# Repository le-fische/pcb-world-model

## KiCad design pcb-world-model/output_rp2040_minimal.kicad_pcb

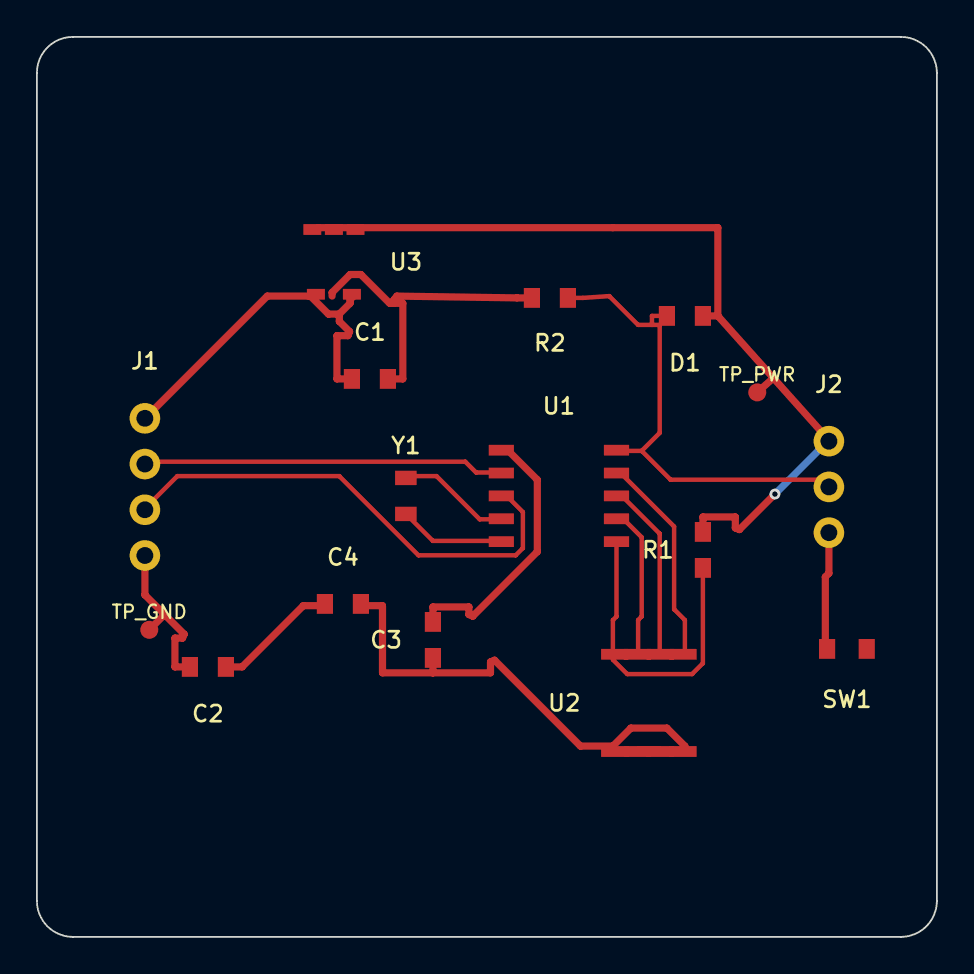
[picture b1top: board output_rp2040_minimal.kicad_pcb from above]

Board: 2 copper layers, 50.0 x 50.0 mm, 16 parts (0 on the bottom side), 12 nets.

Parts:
C1: 10uF_VBUS; C_0805_2012Metric
C2: 100nF_VDD; C_0805_2012Metric
C3: 100nF_CORE; C_0805_2012Metric
C4: 100nF_FLASH; C_0805_2012Metric
D1: PWR_LED; LED_0805_2012Metric
J1: USB_C; USB_C_Receptacle_GCT_USB4085
J2: GPIO_HDR; PinHeader_1x03_P2.54mm_Vertical
R1: 10k_CS; R_0603_1608Metric
R2: 1k_LED; R_0603_1608Metric
SW1: BOOTSEL; SW_SPST_TL3342
TP_GND: TestPoint_Pad_D1.0mm
TP_PWR: TestPoint_Pad_D1.0mm
U1: RP2040; QFN-10_RP2040_Core
U2: W25Q16JV; SOIC-8_3.9x4.9mm_P1.27mm
U3: NCP1117-3.3; SOT-23-5
Y1: 12MHz; Crystal_SMD_3225

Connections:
GND: C1.2, C2.2, C3.2, C4.2, J1.4, J2.3, R2.2, SW1.2, TP_GND.1, U2.5, U2.8, U3.2
LED_STAT: D1.2, J2.2, R2.1, U1.6
QSPI_CLK: U1.9, U2.3
QSPI_CS: R1.2, SW1.1, U1.10, U2.4
QSPI_D0: U1.8, U2.2
QSPI_D1: U1.7, U2.1
USB_DM: J1.2, U1.2
USB_DP: J1.3, U1.3
VBUS_5V: C1.1, J1.1, U3.1, U3.3
VCC_3V3: C2.1, C3.1, C4.1, D1.1, J2.1, R1.1, TP_PWR.1, U1.1, U2.6, U2.7, U3.4, U3.5
XIN: U1.4, Y1.1
XOUT: U1.5, Y1.2

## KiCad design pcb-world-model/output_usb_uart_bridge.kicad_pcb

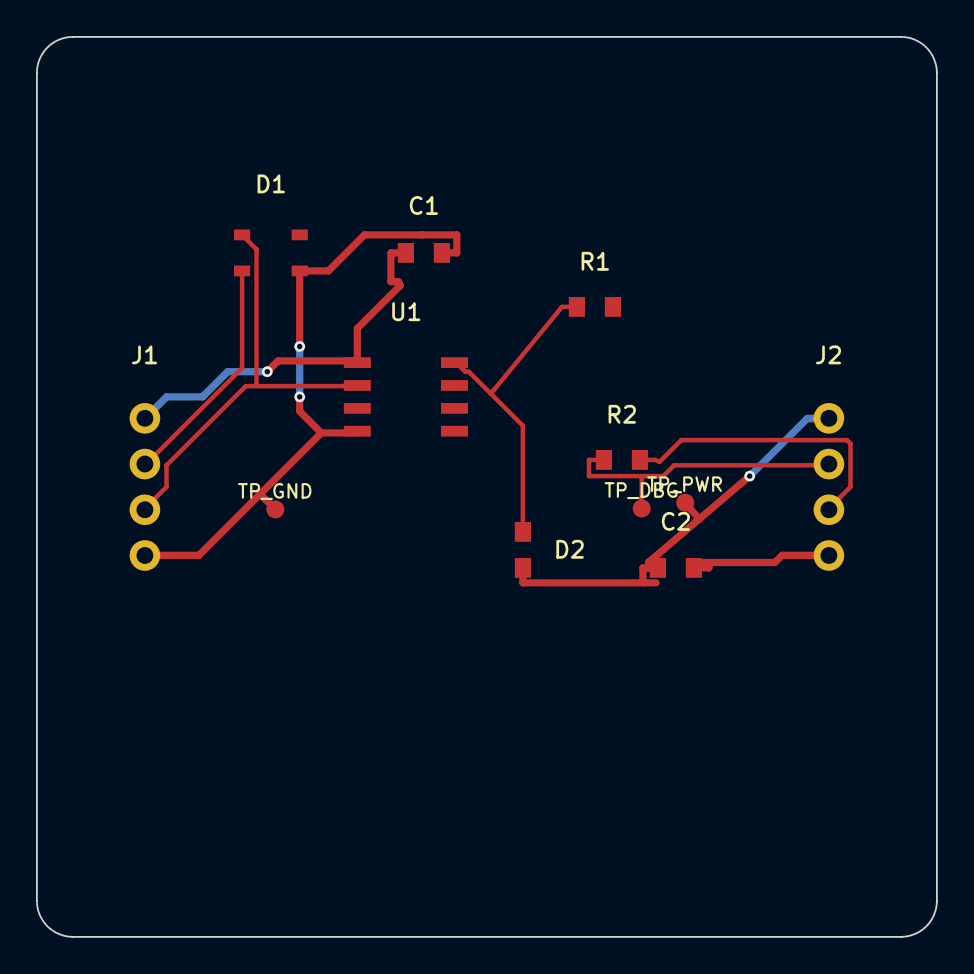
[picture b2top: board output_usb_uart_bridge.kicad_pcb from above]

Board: 2 copper layers, 50.0 x 50.0 mm, 12 parts (0 on the bottom side), 8 nets.

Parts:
C1: 10uF; C_0805_2012Metric
C2: 100nF; C_0805_2012Metric
D1: USBLC6-2SC6; SOT-23-6
D2: TX_LED; LED_0805_2012Metric
J1: USB_PORT; USB_Micro-B_Molex
J2: UART_HDR; PinHeader_1x04_P2.54mm_Vertical
R1: 470R; R_0603_1608Metric
R2: 0R_LOOP_OPT; R_0603_1608Metric
TP_DBG: TestPoint_Pad_D1.0mm
TP_GND: TestPoint_Pad_D1.0mm
TP_PWR: TestPoint_Pad_D1.0mm
U1: CH340N_BRIDGE; SOIC-8_3.9x4.9mm_P1.27mm

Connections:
GND: C1.2, C2.2, D1.3, J1.4, J2.4, R1.2, TP_GND.1, U1.4
LED_ACT: D2.2, R1.1, U1.8
UART_RX: J2.3, R2.2, U1.7
UART_TX: J2.2, R2.1, TP_DBG.1, U1.6
USB_DM: D1.2, J1.2, U1.3
USB_DP: D1.1, J1.3, U1.2
VBUS_5V: C1.1, D1.4, J1.1, U1.1
VCC_3V3: C2.1, D2.1, J2.1, TP_PWR.1, U1.5

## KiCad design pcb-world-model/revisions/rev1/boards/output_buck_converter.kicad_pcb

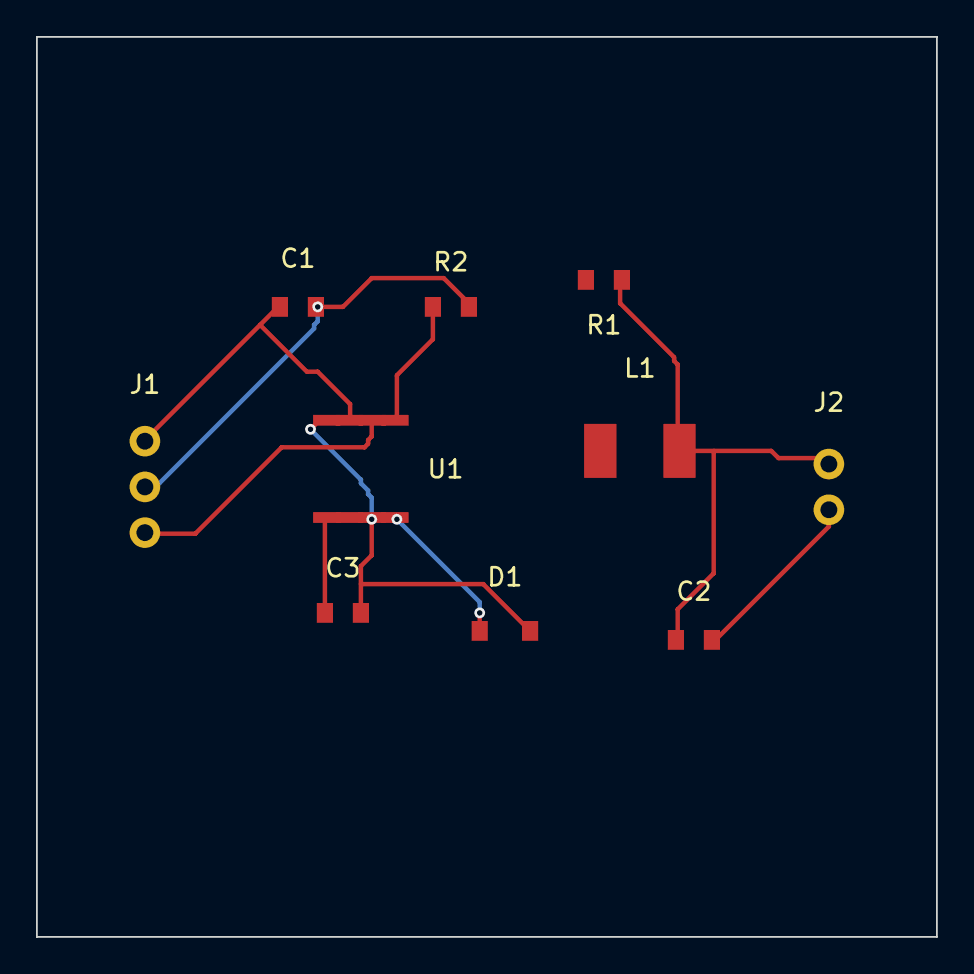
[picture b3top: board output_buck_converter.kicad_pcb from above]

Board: 2 copper layers, 50.0 x 50.0 mm, 10 parts (0 on the bottom side), 7 nets.

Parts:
C1: 22uF_IN; C_1206_3216Metric
C2: 47uF_OUT; C_1206_3216Metric
C3: 100nF_BST; C_0603_1608Metric
D1: SS34; D_SMA
J1: VIN_12V; TerminalBlock_bornier-3_P5.08mm
J2: VOUT_5V; TerminalBlock_bornier-2_P5.08mm
L1: 10uH; L_6.3x6.3_H3
R1: 100k; R_0603_1608Metric
R2: 18.7k; R_0603_1608Metric
U1: TPS54302; SOIC-8_3.9x4.9mm_P1.27mm

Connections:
BOOT: C3.1, U1.1
EN_CTRL: J1.3, U1.6
FB_DIV: R1.2, R2.1, U1.5
GND: C1.2, C2.2, D1.1, J1.2, J2.2, R2.2, U1.4
SW_NODE: C3.2, D1.2, L1.1, U1.3, U1.8
VIN_12V: C1.1, J1.1, U1.2, U1.7
VOUT_5V: C2.1, J2.1, L1.2, R1.1

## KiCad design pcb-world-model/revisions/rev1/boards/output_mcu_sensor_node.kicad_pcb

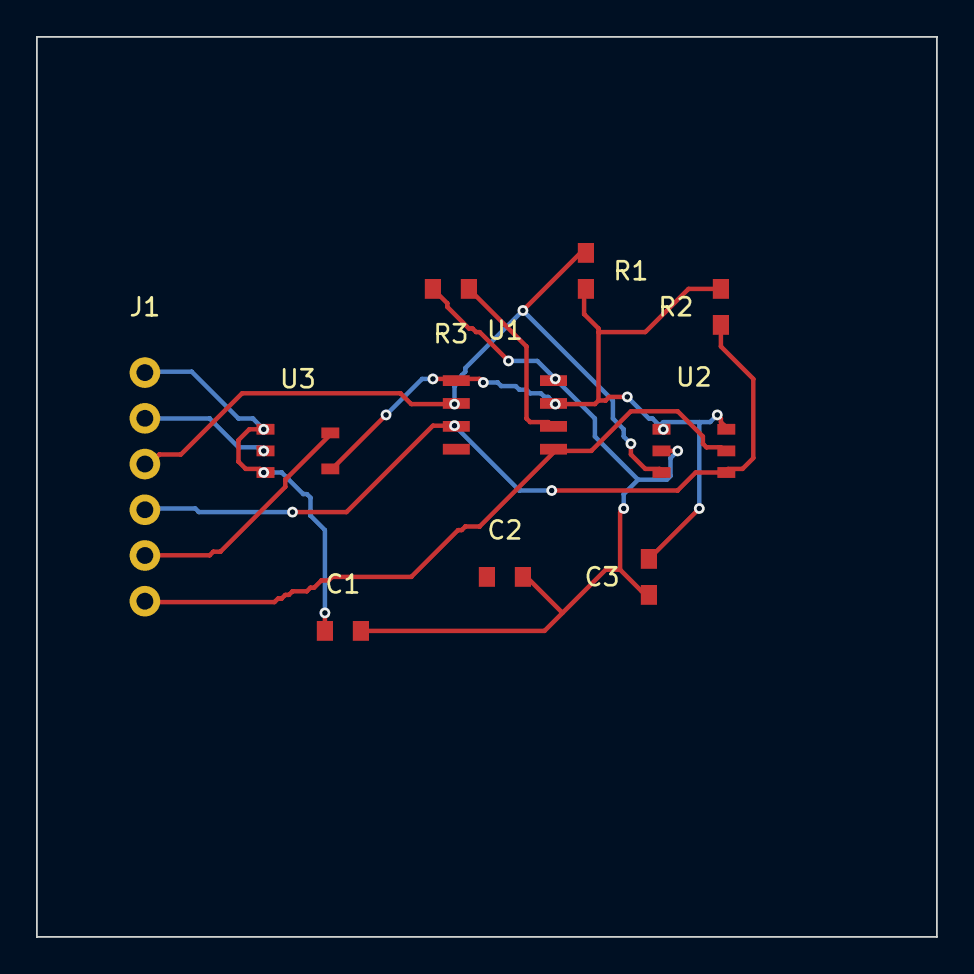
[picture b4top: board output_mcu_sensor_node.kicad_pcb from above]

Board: 2 copper layers, 50.0 x 50.0 mm, 10 parts (0 on the bottom side), 8 nets.

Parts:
C1: 10uF; C_0805_2012Metric
C2, C3: 100nF; C_0805_2012Metric
J1: I2C_HOST_HDR; PinHeader_1x06_P2.54mm_Vertical
R1, R2: 4.7k; R_0603_1608Metric
R3: 1k_LED; R_0603_1608Metric
U1: ATtiny1614; SOIC-8_3.9x4.9mm_P1.27mm
U2: BME280_I2C; SOT-23-6
U3: AP2112K-3.3; SOT-23-5

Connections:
GND: C1.2, C2.2, C3.2, J1.2, R3.2, U1.8, U2.2, U3.2
I2C_SCL: J1.4, R2.2, U1.3, U2.4
I2C_SDA: J1.3, R1.2, U1.2, U2.3
MCU_RST: J1.5, U1.4, U3.5
SENSOR_INT: J1.6, U1.5, U2.5
STATUS_LED: R3.1, U1.6
VCC_3V3: C2.1, C3.1, R1.1, R2.1, U1.1, U1.7, U2.1, U2.6, U3.4
VIN_5V: C1.1, J1.1, U3.1, U3.3

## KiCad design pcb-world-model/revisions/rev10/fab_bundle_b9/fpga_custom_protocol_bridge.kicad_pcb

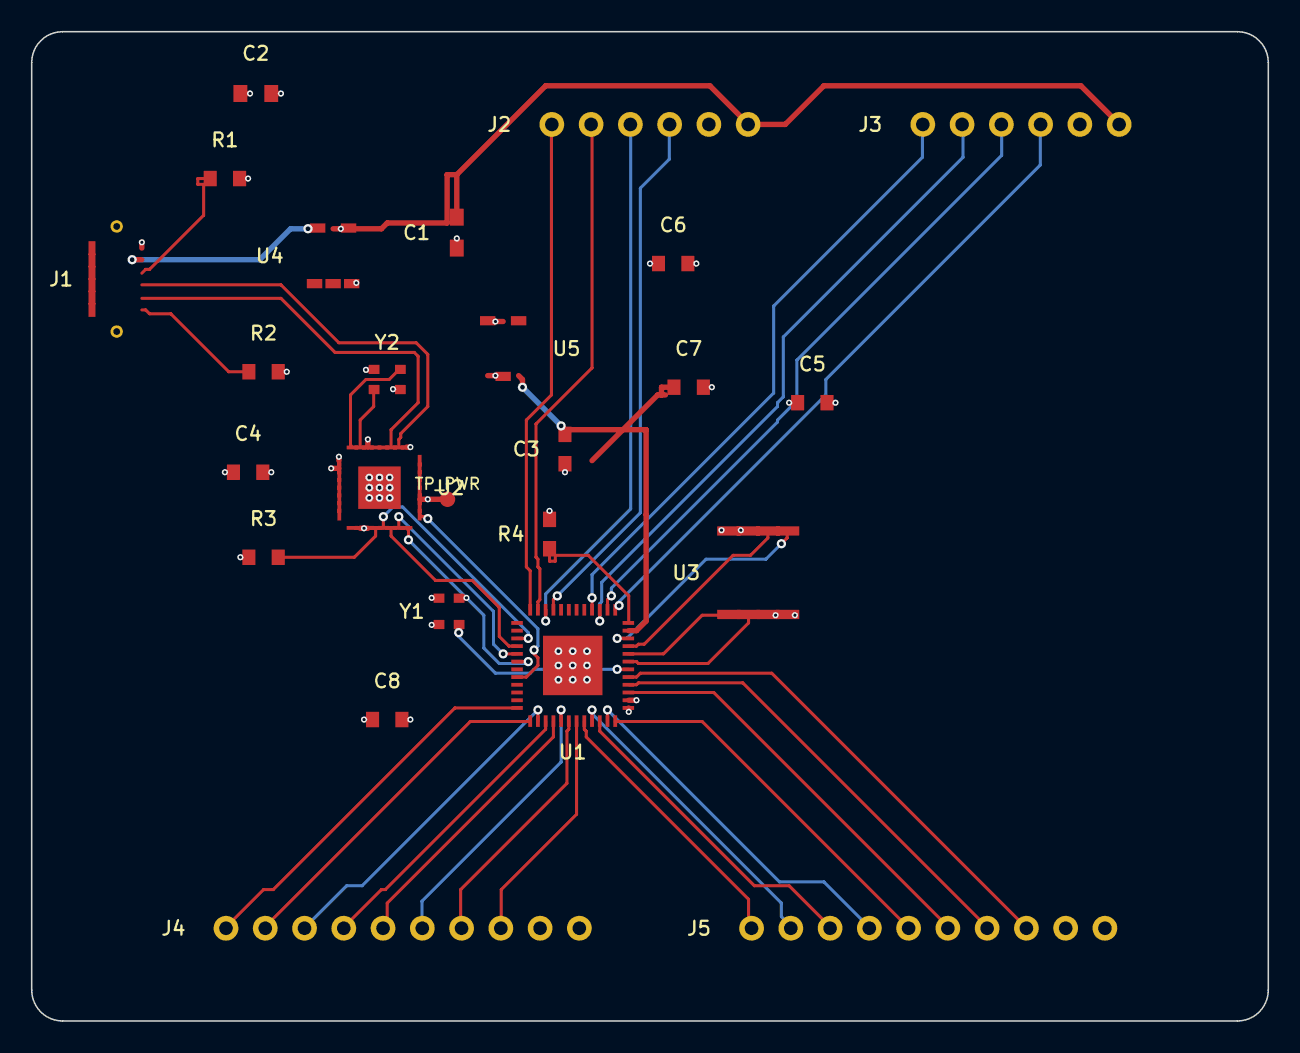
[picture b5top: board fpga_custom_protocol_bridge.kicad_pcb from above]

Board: 4 copper layers, 80.0 x 64.0 mm, 25 parts (0 on the bottom side), 46 nets.

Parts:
C1: 10uF_5V; C_0805_2012Metric
C2: 10uF_3V3; C_0805_2012Metric
C3: 1uF_1V2; C_0603_1608Metric
C4: 100nF_ESP1; C_0603_1608Metric
C5: 100nF_ESP2; C_0603_1608Metric
C6: 100nF_FPGA_IO; C_0603_1608Metric
C7: 100nF_FPGA_CORE; C_0603_1608Metric
C8: 100nF_FLASH; C_0603_1608Metric
J1: USB_C_6P; USB_C_Receptacle_6P
J2: WS2812_CH0_3; PinHeader_1x06_P2.54mm
J3: WS2812_CH4_7; PinHeader_1x06_P2.54mm
J4: ENC_CH0_3; PinHeader_1x10_P2.54mm
J5: ENC_CH4_7; PinHeader_1x10_P2.54mm
R1: 5.1k_CC1; R_0603_1608Metric
R2: 5.1k_CC2; R_0603_1608Metric
R3: 10k_ESP_EN; R_0603_1608Metric
R4: 10k_CRESET; R_0603_1608Metric
TP_PWR: TestPoint_Pad_D1.0mm
U1: Lattice_iCE40UP5K; QFN-48_7.0x7.0mm_P0.5mm
U2: ESP32-C3FN4; QFN-32_5.0x5.0mm_P0.5mm
U3: W25Q16; SOIC-8_3.9x4.9mm_P1.27mm
U4: AP2112K-3.3; SOT-23-5
U5: XC6206; SOT-23-3
Y1, Y2: XTAL_40MHz_2016; Crystal_SMD_2016-4Pin_2.0x1.6mm

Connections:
ENC0_A: J4.3, U1.43
ENC0_B: J4.4, U1.42
ENC1_A: J4.5, U1.41
ENC1_B: J4.6, U1.40
ENC2_A: J4.7, U1.39
ENC2_B: J4.8, U1.38
ENC3_A: J4.9, U1.37
ENC3_B: J4.10, U1.36
ENC4_A: J5.3, U1.5
ENC4_B: J5.4, U1.4
ENC5_A: J5.5, U1.3
ENC5_B: J5.6, U1.48
ENC6_A: J5.7, U1.47
ENC6_B: J5.8, U1.46
ENC7_A: J5.9, U1.45
ENC7_B: J5.10, U1.44
ESP_EN: R3.2, U2.4
ESP_SPI_CS_N: U1.30, U2.8
ESP_SPI_MISO: U1.29, U2.7
ESP_SPI_MOSI: U1.28, U2.6
ESP_SPI_SCK: U1.27, U2.5
ESP_XTAL_N: U2.24, Y2.3
ESP_XTAL_P: U2.23, Y2.1
FLASH_CS_N: U1.10, U3.1
FLASH_MISO: U1.9, U3.2
FLASH_MOSI: U1.8, U3.5
FLASH_SCK: U1.7, U3.6
FPGA_CLK_48M: U1.6, Y1.3
FPGA_CRESET_N: R4.2, U1.12
FPGA_IRQ_N: U1.32, U2.9
GND: C1.2, C2.2, C3.2, C4.2, C5.2, C6.2, C7.2, C8.2, J1.GND, J1.SH1, J1.SH2, J2.2, J3.2, J4.2, J5.2, R1.2, R2.2, U1.2, U1.49, U2.26, U2.33, U3.4, U4.2, U5.1, Y1.2, Y1.4, Y2.2, Y2.4
USB_CC1: J1.CC1, R1.1
USB_CC2: J1.CC2, R2.1
USB_DM: J1.D-, U2.19
USB_DP: J1.D+, U2.18
VBUS_5V: C1.1, J1.VBUS, J2.1, J3.1, U4.1, U4.3
VCC_1V2: C3.1, C7.1, U1.11, U5.2
VCC_3V3: C2.1, C4.1, C5.1, C6.1, C8.1, J4.1, J5.1, R3.1, R4.1, TP_PWR.1, U1.1, U2.2, U2.3, U2.11, U2.17, U2.22, U2.25, U3.3, U3.7, U3.8, U4.5, U5.3, Y1.1
WS_CH0: J2.3, U1.21
WS_CH1: J2.4, U1.22
WS_CH2: J2.5, U1.23
WS_CH3: J2.6, U1.24
WS_CH4: J3.3, U1.13
WS_CH5: J3.4, U1.14
WS_CH6: J3.5, U1.15
WS_CH7: J3.6, U1.16

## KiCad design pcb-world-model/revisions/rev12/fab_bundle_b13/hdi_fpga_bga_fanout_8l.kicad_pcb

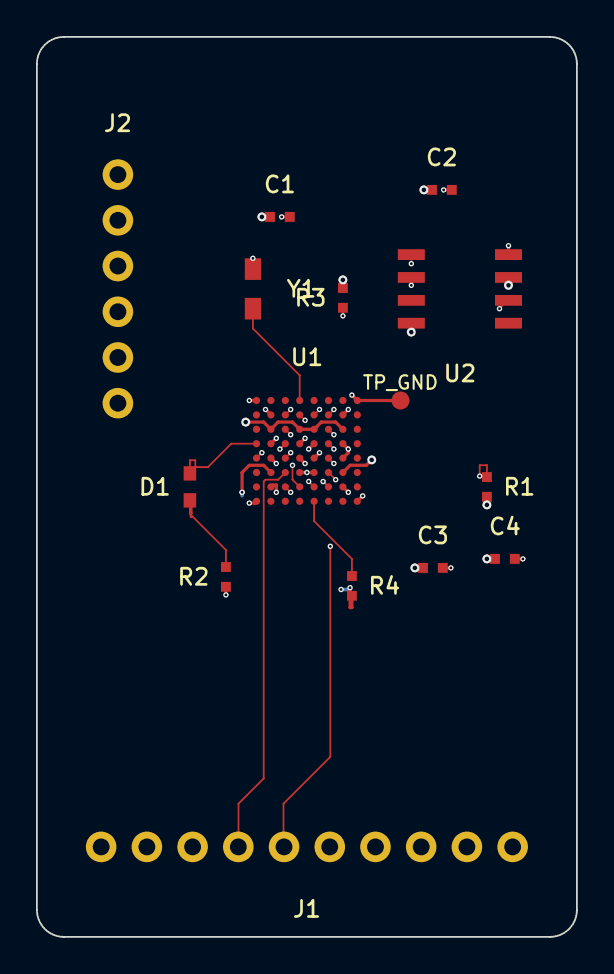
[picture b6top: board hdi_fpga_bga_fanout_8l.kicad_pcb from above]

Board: 8 copper layers, 30.0 x 50.0 mm, 15 parts (0 on the bottom side), 23 nets.

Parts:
C1, C2, C3, C4: 100nF; C_0402_1005Metric
D1: STAT_LED; LED_0603_1608Metric
J1: HS_BUS_HDR; PinHeader_1x10_P2.54mm_Horizontal
J2: SPI_JTAG_HDR; PinHeader_1x06_P2.54mm_Vertical
R1: 10k_CS; R_0402_1005Metric
R2: 330R_LED; R_0402_1005Metric
R3: 10k_RST; R_0402_1005Metric
R4: 10k_RX; R_0402_1005Metric
TP_GND: TestPoint_Pad_D1.0mm
U1: ECP5-BGA64; BGA-64_7.2x7.2mm_Layout8x8_P0.8mm
U2: W25Q16_QSPI; SOIC-8_3.9x4.9mm_P1.27mm
Y1: 25MHz_OSC; Crystal_SMD_3225

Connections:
CLK_25M: U1.A4, Y1.1
GND: C1.2, C2.2, C3.2, C4.2, J1.10, J2.2, R2.2, TP_GND.1, U1.A1, U1.A8, U1.B2, U1.B7, U1.D2, U1.D4, U1.D5, U1.D7, U1.E2, U1.E4, U1.E5, U1.E7, U1.F4, U1.F5, U1.G2, U1.G7, U1.H1, U1.H8, U2.4, Y1.2
HS_BUS_0: J1.1, U1.C3
HS_BUS_1: J1.2, U1.C6
HS_BUS_2: J1.3, U1.D3
HS_BUS_3: J1.4, U1.D6
HS_BUS_4: J1.5, U1.E3
HS_BUS_5: J1.6, U1.E6
HS_BUS_6: J1.7, U1.F3
HS_BUS_7: J1.8, U1.F6
LED_DRV: D1.1, U1.D1
LED_K: D1.2, R2.1
QSPI_CS: R1.2, U1.B4, U2.1
QSPI_IO0: U1.B5, U2.5
QSPI_IO1: U1.B6, U2.2
QSPI_SCK: U1.B3, U2.6
RESET_N: R3.2, U1.E1, U2.7
SPI_CS: J2.6, U1.G6
SPI_MISO: J2.4, U1.G4
SPI_MOSI: J2.3, U1.G3
SPI_SCK: J2.5, U1.G5
UART_RX: R4.2, U1.H5
VCC_3V3: C1.1, C2.1, C3.1, C4.1, J1.9, J2.1, R1.1, R3.1, R4.1, U1.C2, U1.C4, U1.C5, U1.C7, U1.F2, U1.F7, U2.3, U2.8

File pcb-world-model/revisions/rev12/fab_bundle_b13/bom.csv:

Comment,Designator,Footprint,Quantity
100nF,"C1,C2,C3,C4",Capacitor_SMD:C_0402_1005Metric,4
STAT_LED,D1,LED_SMD:LED_0603_1608Metric,1
HS_BUS_HDR,J1,Connector_PinHeader_2.54mm:PinHeader_1x10_P2.54mm_Horizontal,1
SPI_JTAG_HDR,J2,Connector_PinHeader_2.54mm:PinHeader_1x06_P2.54mm_Vertical,1
10k_CS,R1,Resistor_SMD:R_0402_1005Metric,1
330R_LED,R2,Resistor_SMD:R_0402_1005Metric,1
10k_RST,R3,Resistor_SMD:R_0402_1005Metric,1
10k_RX,R4,Resistor_SMD:R_0402_1005Metric,1
ECP5-BGA64,U1,Package_BGA:BGA-64_7.2x7.2mm_Layout8x8_P0.8mm,1
W25Q16_QSPI,U2,Package_SO:SOIC-8_3.9x4.9mm_P1.27mm,1
25MHz_OSC,Y1,Crystal:Crystal_SMD_3225,1
